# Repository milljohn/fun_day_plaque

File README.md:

# Fun Day Plaque

A simple Neoplixel plaque using an ATTINY85. For a cool trophy.

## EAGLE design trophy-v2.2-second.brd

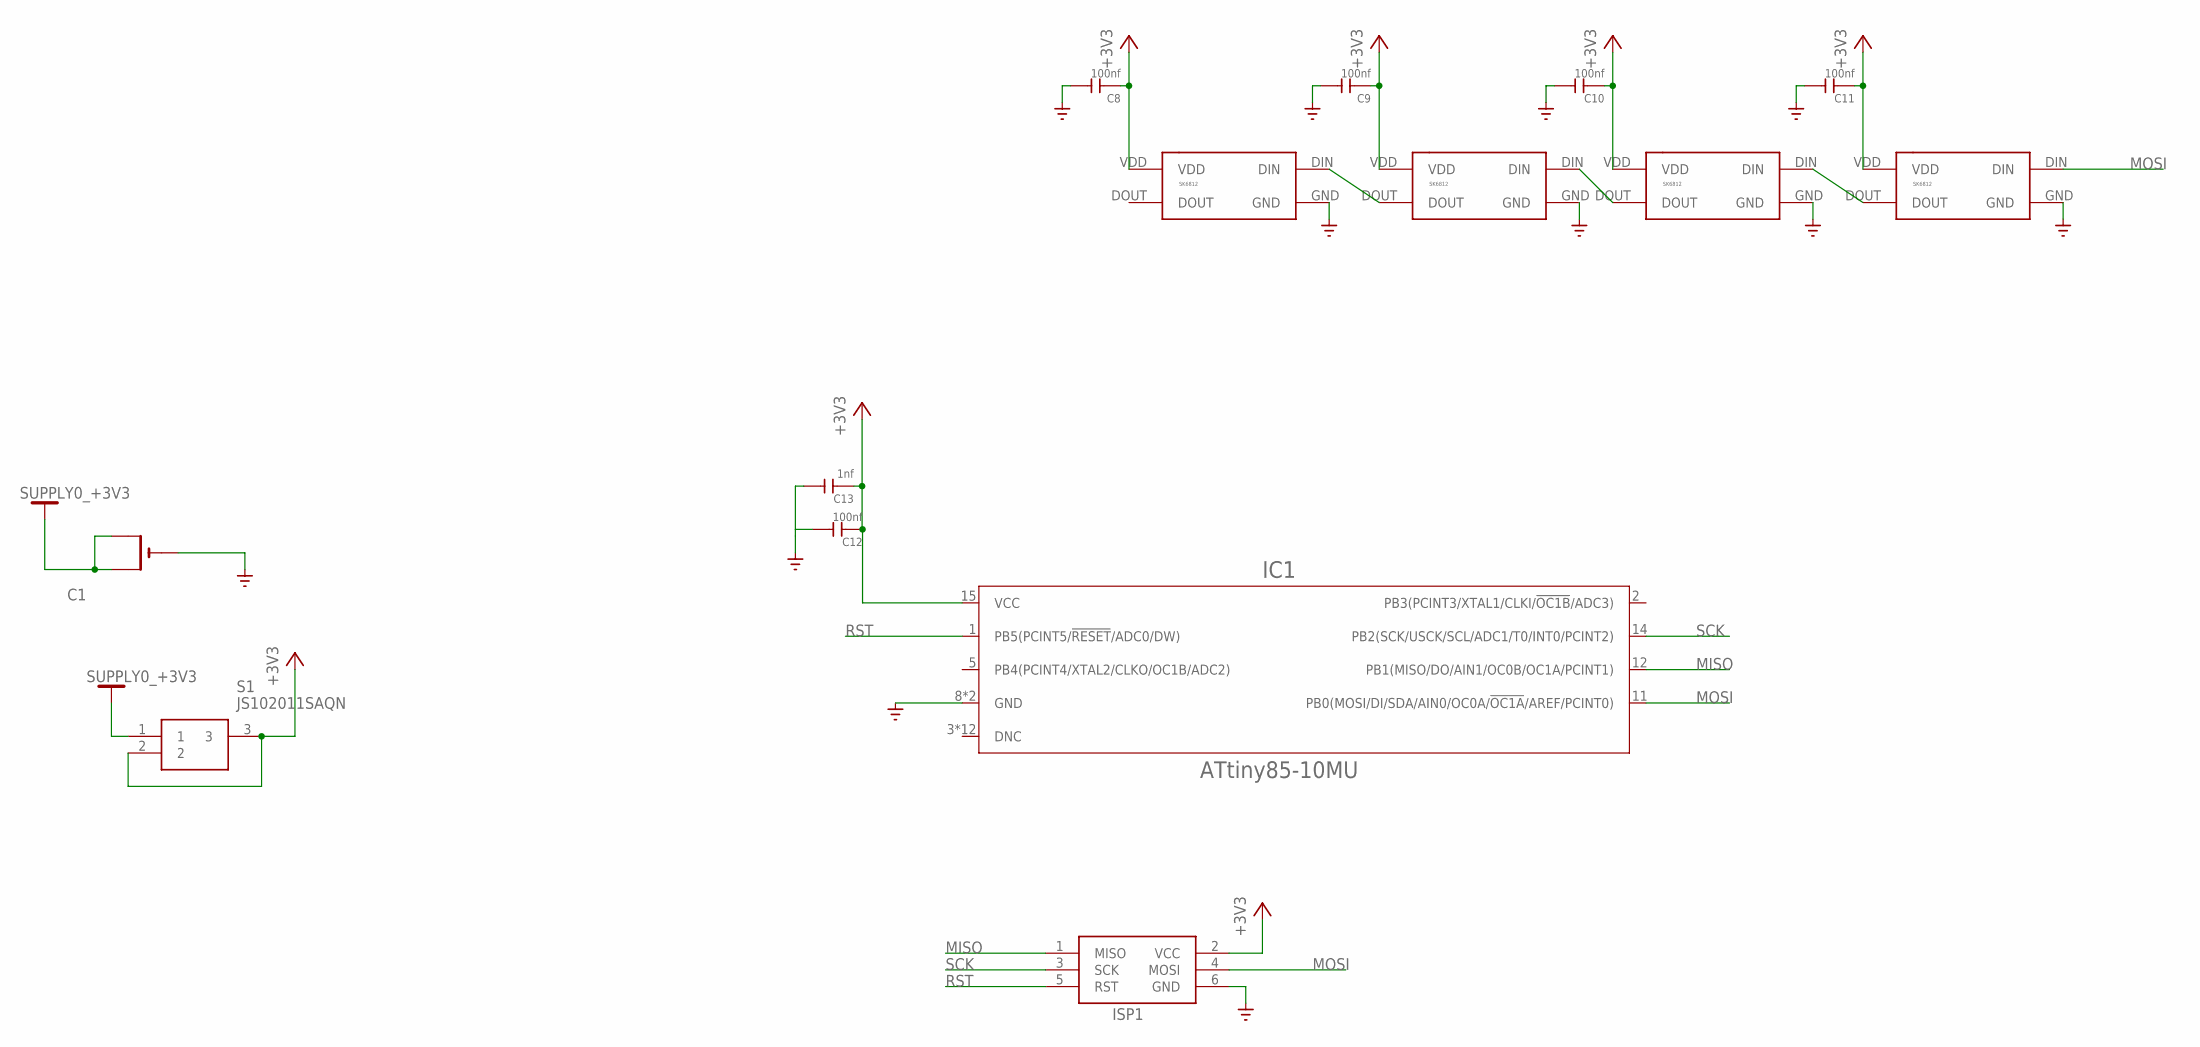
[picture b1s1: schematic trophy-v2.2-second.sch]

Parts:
C1: CL2020; CR2032-SMD
C8, C9, C10, C11, C12: 100nf; C0603
C13: 1nf; C0603
IC1: ATtiny85-10MU; QFN50P400X400X80-21T275
ISP1: AVRISP-6; AVRISP
S1: JS102011SAQN
U$1, U$2, U$3, U$4: SK6812; 5050

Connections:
+3V3: C8.1, C9.1, C10.1, C11.1, C12.1, C13.1, IC1.15 (VCC), ISP1.2 (VCC), S1.2, S1.3, U$1.VDD, U$2.VDD, U$3.VDD, U$4.VDD
+3V3-BAT: C1.+$1 (+), C1.+$2 (+1), S1.1
GND: C1.-, C8.2, C9.2, C10.2, C11.2, C12.2, C13.2, IC1.8 (GND), IC1.21 (GND), ISP1.6 (GND), U$1.GND, U$2.GND, U$3.GND, U$4.GND
MISO: IC1.12 (PB1(MISO/DO/AIN1/OC0B/OC1A/PCINT1)), ISP1.1 (MISO)
MOSI: IC1.11 (PB0(MOSI/DI/SDA/AIN0/OC0A/!OC1A!/AREF/P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), ISP1.4 (MOSI), U$1.DIN
unnamed: U$3.DOUT, U$4.DIN
unnamed: U$2.DOUT, U$3.DIN
unnamed: U$1.DOUT, U$2.DIN
RST: IC1.1 (PB5(PCINT5/!RESET!/ADC0/DW)), ISP1.5 (RST)
SCK: IC1.14 (PB2(SCK/USCK/SCL/ADC1/T0/INT0/PCINT2)), ISP1.3 (SCK)

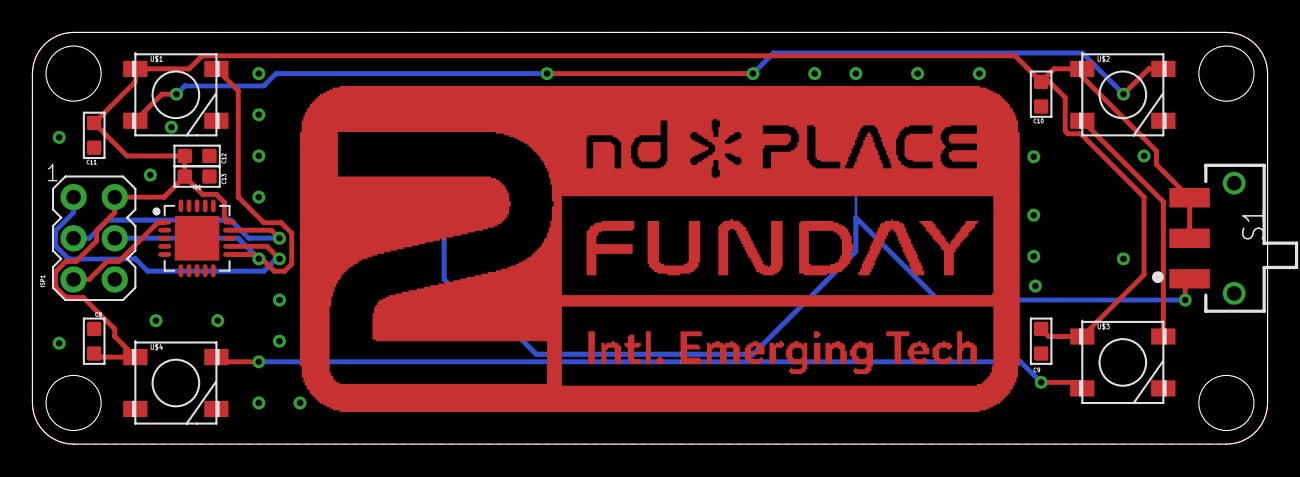
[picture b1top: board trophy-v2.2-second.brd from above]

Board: 2 copper layers, 76.2 x 25.4 mm, 14 parts (1 on the bottom side), 10 nets.

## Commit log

2022-10-15 add cam files
2022-10-19 V2 layout change, battery on back, text removed
2022-10-19 minor ground fix, vector art test
2022-10-19 add first place board
2022-10-19 add second and third place
